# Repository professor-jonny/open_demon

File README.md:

# Open Demon Project

## Overview:
This project is an open-source recreation of the Team Xecuter Demon, a powerful multi-function NAND device for the Xbox 360. Our goal is to rebuild the firmware, fix existing bugs, and potentially develop new hardware add-ons. We hope this project encourages wider community involvement.

## Demon background:
Released in February 2012 alongside a J-Runner update, the Demon offered an all-in-one solution for NAND programming. While initially successful, it was perhaps over-hyped and ultimately didn't achieve the same market penetration as other Team Xecuter devices. The rise of stealth services further diminished its relevance, and the lack of promised add-on hardware hampered its potential. Numerous planned add-ons never saw a public release due to Team Xecuter's internal challenges. Following financial and legal difficulties, ownership transitioned from K3 to Max.

The Demon provides access to the console's UART for direct interaction, along with extensive onboard I/O capable of supporting a separate 8-bit bus. Additional I/O pins are available for bit-banging SPI, I2C, or other protocols. Although Team Xecuter announced Android and iOS remote control apps in July 2012, these were never released. Similarly, LCD support was explored, with prototypes circulated among developers, but only the NAND switching plugin, Switch!, was officially launched.

## Project Background:
Inspired by discussions with fellow enthusiasts and analysis of the Xbox 360 ODE cracking process, this project began with recreating the Demon's schematics. Access to images of a pre-release slim PCB aided in verification.

Understanding the hardware, components, and design is crucial for reverse engineering. One undocumented aspect is controlling the Demon's hardware and I/O from the console. We aim to document the I/O addressing scheme (if implemented) and investigate the potential for a UART control API. A PC-based USB control API already exists. Third-party add-ons could leverage the Demon's I/O, potentially enabling features like an integrated LCD display.

## Theory of operation:
The Demon's NAND interface largely mirrors the console's onboard NAND, using a tri-state bus transceiver to isolate the microcontroller from the NAND control logic. Control appears to rely on the CE and RB signals, with other control lines interrupted by the transceiver. Logic in U3 prevents simultaneous driving of both CE pins. C3 likely introduces timing delays for CE switching to the Demon's NAND via NOR gates in U4. This, combined with RB, likely determines chip readiness before OE activates, hijacking CE to enable the Demon's NAND. OE also enables the tri-state transceiver and Demon's NAND CE logic when the motherboard's CE is high.

The design seemingly intercepts NAND control between read/write cycles, asserting and locking control while the chip is busy. Analyzing microcontroller-to-NAND communication is necessary for confirmation, but this theory appears plausible.

## Challenges:
The AT90USB microcontroller's bootloader employs custom encryption (believed to be RSA-2048), posing significant challenges. Existing Team Xecuter firmware is unanalyzable, current devices require a bootloader update for compatibility, and a new bootloader would break existing firmware support. Developing new firmware for the current bootloader is blocked by signature checks.

Project advancement hinges on recovering the bootloader or its RSA key. Collaboration with experienced individuals is sought. Donations are welcome to support this effort. While various options have been considered, we remain open to suggestions. Contact is being attempted with the original Team Xecuter developer. Interest exists in manufacturing the device if the bootloader is recovered. Due to on-the-fly firmware unpacking, direct firmware analysis is infeasible. A brown-out reset glitch or physical access is likely required for bootloader recovery. Cracking the RSA key is computationally infeasible.

For this project to go forward I would like to recover the bootloader or at least the RSA key by attacking the microcontroller if any one has experience with this or would be willing to try this it would be awesome if you would contact me.
I don't fancy dropping $1400usd to a chineese firm to do this I would rather give this to a fellow Xbox or scene hacker as this is beyond my skill and a very special area.
I already have a few buddies who would be willing to donate to the cause, So far I have resisted going down the route of croud sourcing the project as realistically I don't think niche projects like this work well on that platform and i'd like to aviod the disapointment for everyone when it fails.
You are welcome to donate to the cause if you wish id love a failed demon hardware so i can fully recreate PCB's.

I'd like to keep it all open source if possible, or it close it for a time to make hardware to recoup costs if we were to fund bootloader recovery there is a whole lot of options I have not explored here and I'm open to suggestions.

I have atempted to contact the original Team Xecuter dev involved with the design and programming of the demon project but have had no luck in getting a reply sadly so it is what it is.

I already have people intrested in manufacturing the device if we do manage to progress futher and recover the bootloader there is intrest to recreate them.

The demon seems to unpack the firmware on the fly and write it to the onbord flash so there is no attack vector there and we would need to preform brown out reset glitch or physical access to recover the bootloader for reverse engineering to get the RSA key.

RSA is currently secure and would take a supercomputer decades to crack the firmware update key embeded within the bootloader.

## Project Outline/ Future Plans:
The future plan is to recrate the 
The primary goal is an open-source Demon recreation, initially compatible with existing hardware. A hardware revision is likely due to component discontinuation. A more ambitious objective involves a new FPGA-based device with a microcontroller. This would enable on-the-fly NAND image creation, kernel patching, and a console configuration app. A shared memory window could facilitate console-microcontroller communication for RAM offloading, code relocation, and coprocessing.

Eaton's testing indicates a NAND bus speed of approximately 1.4 Mbps, suitable for low-bandwidth operations. The impact of using faster media is unknown. This advanced design requires skilled FPGA/CPLD developers. More information is available on 

Eaton's blog:
[eaton works](https://eaton-works.com/2023/01/09/how-microsoft-attempted-to-make-the-xbox-360-dashboard-load-faster/)

The schematics were designed using Eagle:
[Autodesk Eagle]( https://www.autodesk.com/products/eagle/free-download)

## Licensing
This project is open-source. Hardware and schematics are licensed under the [CERN OHL v.2.0.](https://ohwr.org/cernohl).

Donations are welcome to support XBMC4XBOX, Team Resurgent, or other Xbox resources.

[Teamresurgent donate]( https://www.patreon.com/teamresurgent)
[xbmc4xbox donate](https://www.xbmc4xbox.org.uk/donate/)

## Disclaimer
This project is a work in progress and may contain inaccuracies. Feedback and corrections are welcome. Development is ongoing, and Gerber files for all Demon variants will be released eventually. A preliminary Phat PCB design is available.
This project is by no meany complete or possibly accurate it is my own account of insight may be incorect, and I'm open to suggestions and correctons.

## Acknowledgements
We thank Coz, Goobycorp, and Eaton for their invaluable contributions.

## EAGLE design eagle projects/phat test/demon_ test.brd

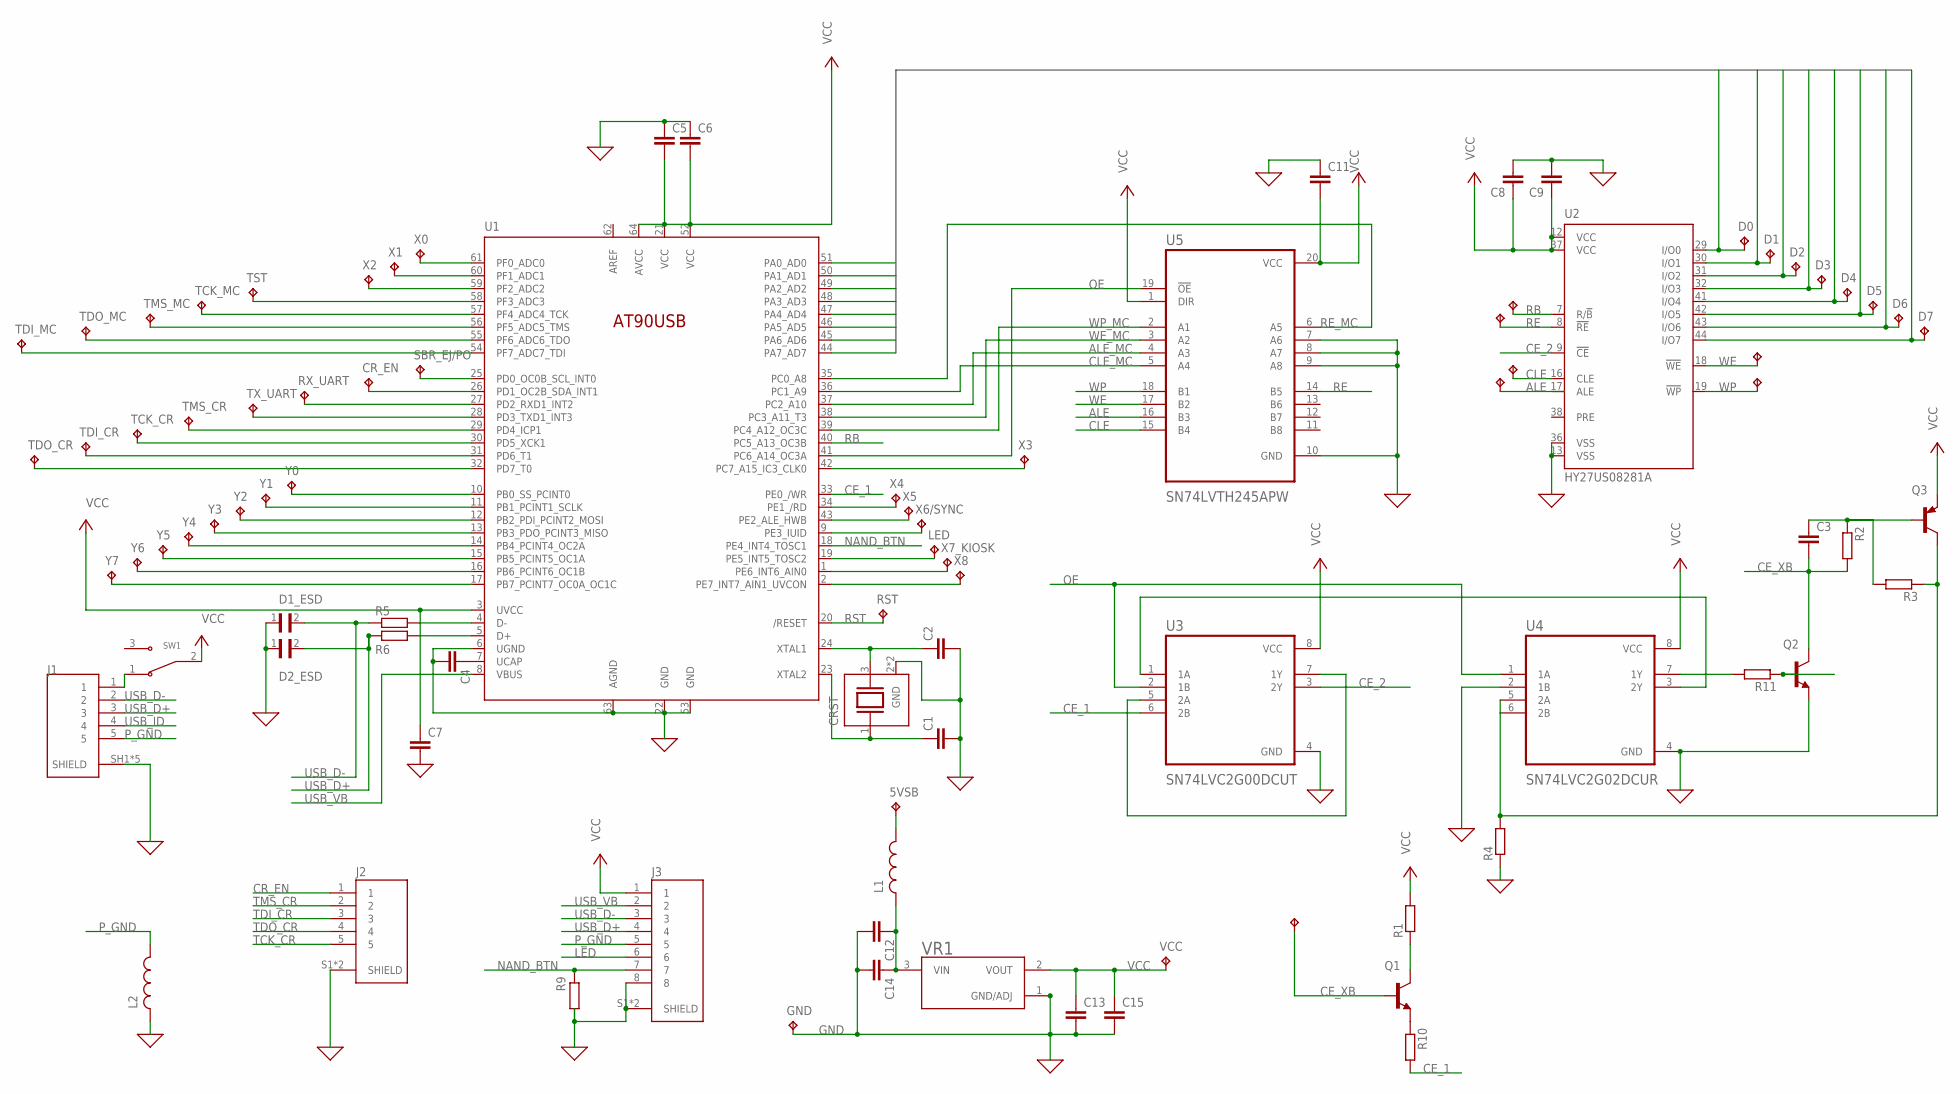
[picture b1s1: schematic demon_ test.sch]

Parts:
5VSB: TPTP20R; TP20R
ALE1: TPTP15R; TP15R
C1, C2: 18pf; C0603
C3: 47pf; C0603
C4, C11: 1uf; C0603
C5, C6, C7, C8, C9, C12: .1uf; C0603
C13: 2.2uf tant; C2012
C14: 1uf tant; C2012
C15: 10uf Tant; C2012
CE: TPTP15R; TP15R
CLE1: TPTP15R; TP15R
CRST: ABMM2-8.000MHZ-E2-T; XTAL_ABMM2-8.000MHZ-E2-T
CR_EN: TPTP15R; TP15R
D0, D1, D2, D3, D4, D5, D6, D7: TPTP15R; TP15R
D1_ESD, D2_ESD: PGB1010603; ESD_PGB1010603MR
GND: TPTP15R; TP15R
J1: UJ2-MIBH2-4-SMT; CUI_UJ2-MIBH2-4-SMT
J2: FFC3B07-05-T; GCT_FFC3B07-05-T
J3: FFC3B07-08-T; GCT_FFC3B07-08-T
L1, L2: LQW2BAS6N8J00L; INDC2015X152N
LED: TPTP15R; TP15R
Q1, Q2: BC846; SOT23
Q3: bc856; SOT23-BEC
R1, R6: 22R 5%; R0603
R2: 470R 5%; R0603
R3: 2k7R 5%; R0603
R4: 330R 5%; R0603
R5: 22r 5%; R0603
R9: 10kR 5%; R0603
R10: 68R 5%; R0603
R11: 680R 5%; R0603
RB1: TPTP15R; TP15R
RE: TPTP15R; TP15R
RST: TPTP15R; TP15R
RX_UART: TPTP15R; TP15R
SBR_EJ/PO: TPTP15R; TP15R
SW1: EG1215AA; SW_EG1215AA
TCK_CR: TPTP15R; TP15R
TCK_MC: TPTP15R; TP15R
TDI_CR: TPTP15R; TP15R
TDI_MC: TPTP15R; TP15R
TDO_CR: TPTP15R; TP15R
TDO_MC: TPTP15R; TP15R
TMS_CR: TPTP15R; TP15R
TMS_MC: TPTP15R; TP15R
TST: TPTP15R; TP15R
TX_UART: TPTP15R; TP15R
U1: AT90USB-QFN; QFN64
U2: HY27US08281A; TSOP48
U3: SN74LVC2G00DCUT; SOP50P310X90-8N
U4: SN74LVC2G02DCUR; SOP50P310X90-8N
U5: SN74LVTH245APW; SOP65P640X120-20N
VCC: TPTP15R; TP15R
VR1: AMS1117-3.3; SOT229P700X180-4N
WE1: TPTP15R; TP15R
WP1: TPTP15R; TP15R
X0, X1, X2, X3, X4, X5, X6/SYNC, X7_KIOSK, X8: TPTP15R; TP15R
Y0, Y1, Y2, Y3, Y4, Y5, Y6, Y7: TPTP15R; TP15R

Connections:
0: C7.2, U5.7 (A6), U5.8 (A7), U5.9 (A8), U5.10 (GND)
ALE: ALE1.TP, U2.17 (ALE), U5.16 (B3)
ALE_MC: U1.37 (PC2_A10), U5.4 (A3)
AREF: U1.62 (AREF)
CE_1: R10.2, U1.33 (PE0_/WR), U3.6 (2B)
CE_2: U2.9 (!CE), U3.3 (2Y)
CE_XB: C3.2, CE.TP, Q1.1 (B), Q2.3 (C), R2.2
CLE: CLE1.TP, U2.16 (CLE), U5.15 (B4)
CLE_MC: U1.36 (PC1_A9), U5.5 (A4)
CR_EN: CR_EN.TP, J2.1, U1.26 (PD1_OC2B_SDA_INT1)
D0: D0.TP, U1.51 (PA0_AD0), U2.29 (I/O0)
D1: D1.TP, U1.50 (PA1_AD1), U2.30 (I/O1)
D2: D2.TP, U1.49 (PA2_AD2), U2.31 (I/O2)
D3: D3.TP, U1.48 (PA3_AD3), U2.32 (I/O3)
D4: D4.TP, U1.47 (PA4_AD4), U2.41 (I/O4)
D5: D5.TP, U1.46 (PA5_AD5), U2.42 (I/O5)
D6: D6.TP, U1.45 (PA6_AD6), U2.43 (I/O6)
D7: D7.TP, U1.44 (PA7_AD7), U2.44 (I/O7)
F_5VSB: C12.1, C14.1, L1.1, VR1.3 (VIN)
GND: C1.2, C2.2, C4.2, C5.1, C6.1, C8.2, C9.2, C11.1, C12.2, C13.2, C14.2, C15.2, CRST.2 (GND), CRST.4 (GND), D1_ESD.1, D2_ESD.1, GND.TP, J1.SH1 (SHIELD), J1.SH2 (SHIELD), J1.SH3 (SHIELD), J1.SH4 (SHIELD), J1.SH5 (SHIELD), J2.S1 (SHIELD), J2.S2 (SHIELD), J3.8, J3.S1 (SHIELD), J3.S2 (SHIELD), L2.1, Q2.2 (E), R4.1, R9.2, U1.6 (UGND), U1.22 (GND), U1.53 (GND), U1.63 (AGND), U2.13 (VSS), U2.36 (VSS), U3.4 (GND), U4.2 (1B), U4.4 (GND), VR1.1 (GND/ADJ)
LED: J3.6, LED.TP, U1.19 (PE5_INT5_TOSC2)
unnamed: R5.2, U1.4 (D-)
unnamed: C3.1, Q3.B, R2.1, R3.2
unnamed: C4.1, U1.7 (UCAP)
unnamed: R6.2, U1.5 (D+)
unnamed: Q1.3 (C), R1.1
unnamed: Q1.2 (E), R10.1
unnamed: 5VSB.TP, L1.2
unnamed: U3.5 (2A), U3.7 (1Y)
unnamed: U3.1 (1A), U4.3 (2Y)
unnamed: R11.2, U4.7 (1Y)
unnamed: Q2.1 (B), R11.1
unnamed: Q3.C, R3.1, R4.2, U4.5 (2A), U4.6 (2B)
unnamed: J1.1, SW1.1
NAND_BTN: J3.7, R9.1, U1.18 (PE4_INT4_TOSC1)
OE: U1.41 (PC6_A14_OC3A), U3.2 (1B), U4.1 (1A), U5.19 (!OE)
P_GND: J1.5, J3.5, L2.2
RB: RB1.TP, U1.40 (PC5_A13_OC3B), U2.7 (R/!B)
RE: RE.TP, U2.8 (!RE), U5.14 (B5)
RE_MC: U1.35 (PC0_A8), U5.6 (A5)
RST: RST.TP, U1.20 (/RESET)
RX_UART: RX_UART.TP, U1.27 (PD2_RXD1_INT2)
SBR: SBR_EJ/PO.TP, U1.25 (PD0_OC0B_SCL_INT0)
TCK_CR: J2.5, TCK_CR.TP, U1.30 (PD5_XCK1)
TCK_MC: TCK_MC.TP, U1.57 (PF4_ADC4_TCK)
TD0_MC: TDO_MC.TP, U1.55 (PF6_ADC6_TDO)
TDI_CR: J2.3, TDI_CR.TP, U1.31 (PD6_T1)
TDI_MC: TDI_MC.TP, U1.54 (PF7_ADC7_TDI)
TDO_CR: J2.4, TDO_CR.TP, U1.32 (PD7_T0)
TMS_CR: J2.2, TMS_CR.TP, U1.29 (PD4_ICP1)
TMS_MC: TMS_MC.TP, U1.56 (PF5_ADC5_TMS)
TST: TST.TP, U1.58 (PF3_ADC3)
TX_UART: TX_UART.TP, U1.28 (PD3_TXD1_INT3)
USB_D+: D2_ESD.2, J1.3, J3.4, R6.1
USB_D-: D1_ESD.2, J1.2, J3.3, R5.1
USB_ID: J1.4
USB_VB: J3.2, U1.8 (VBUS)
VCC: C5.2, C6.2, C7.1, C8.1, C9.1, C11.2, C13.1, C15.1, J3.1, Q3.E, R1.2, SW1.2, U1.3 (UVCC), U1.21 (VCC), U1.52 (VCC), U1.64 (AVCC), U2.12 (VCC), U2.37 (VCC), U3.8 (VCC), U4.8 (VCC), U5.1 (DIR), U5.20 (VCC), VCC.TP, VR1.2 (VOUT)
WE: U2.18 (!WE), U5.17 (B2), WE1.TP
WE_MC: U1.38 (PC3_A11_T3), U5.3 (A2)
WP: U2.19 (!WP), U5.18 (B1), WP1.TP
WP_MC: U1.39 (PC4_A12_OC3C), U5.2 (A1)
X0: U1.61 (PF0_ADC0), X0.TP
X1: U1.60 (PF1_ADC1), X1.TP
X2: U1.59 (PF2_ADC2), X2.TP
X3: U1.42 (PC7_A15_IC3_CLK0), X3.TP
X4: U1.34 (PE1_/RD), X4.TP
X5: U1.43 (PE2_ALE_HWB), X5.TP
X6/SYNC: U1.9 (PE3_IUID), X6/SYNC.TP
X7: U1.1 (PE6_INT6_AIN0), X7_KIOSK.TP
X8: U1.2 (PE7_INT7_AIN1_UVCON), X8.TP
XTAL1: C2.1, CRST.3 (2), U1.24 (XTAL1)
XTAL2: C1.1, CRST.1, U1.23 (XTAL2)
Y0: U1.10 (PB0_SS_PCINT0), Y0.TP
Y1: U1.11 (PB1_PCINT1_SCLK), Y1.TP
Y2: U1.12 (PB2_PDI_PCINT2_MOSI), Y2.TP
Y3: U1.13 (PB3_PDO_PCINT3_MISO), Y3.TP
Y4: U1.14 (PB4_PCINT4_OC2A), Y4.TP
Y5: U1.15 (PB5_PCINT5_OC1A), Y5.TP
Y6: U1.16 (PB6_PCINT6_OC1B), Y6.TP
Y7: U1.17 (PB7_PCINT7_OC0A_OC1C), Y7.TP

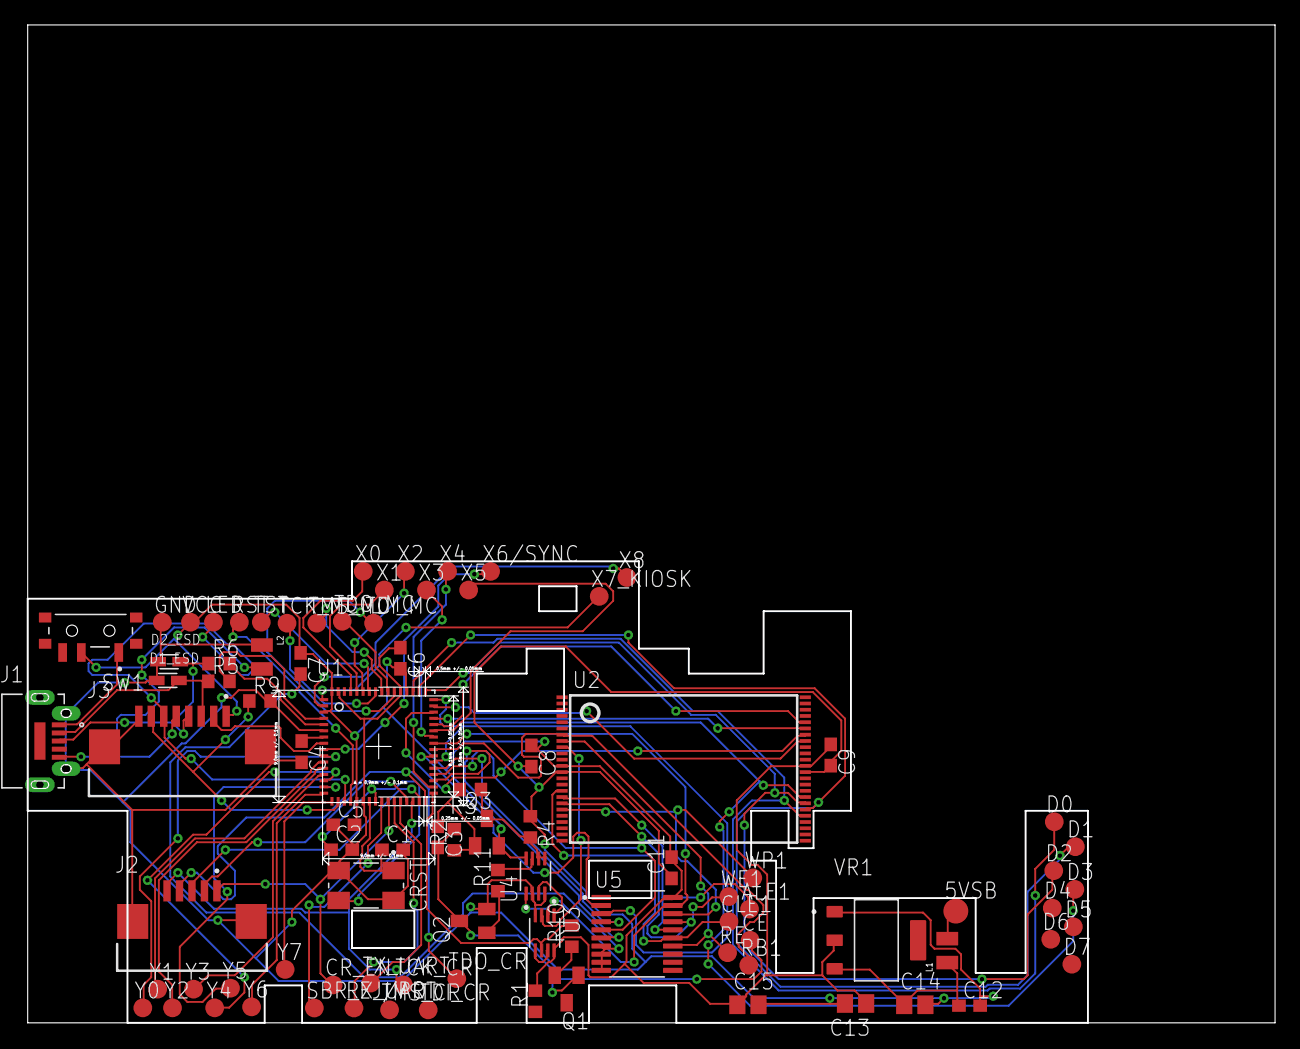
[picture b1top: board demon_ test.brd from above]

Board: 2 copper layers, 99.9 x 79.9 mm, 91 parts (0 on the bottom side), 79 nets.

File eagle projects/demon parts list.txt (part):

Partlist

Exported from demon.sch at 27/03/2023 12:23 pm

EAGLE Version 9.6.2 Copyright (c) 1988-2020 Autodesk, Inc.

Assembly variant: 

Part      Value               Device               Package                  Library                   Sheet

5VSB      TPTP20R             TPTP20R              TP20R                    testpad                   1
ALE1      TPTP15R             TPTP15R              TP15R                    testpad                   1
C1        18pf                C-EUC0603            C0603                    rcl                       1
C2        18pf                C-EUC0603            C0603                    rcl                       1
C3        47pf                C-EUC0603            C0603                    rcl                       1
C4        1uf                 C-EUC0603            C0603                    rcl                       1
C5        .1uf                C-EUC0603            C0603                    rcl                       1
C6        .1uf                C-EUC0603            C0603                    rcl                       1
C7        .1uf                C-EUC0603            C0603                    rcl                       1
C8        .1uf                C-EUC0603            C0603                    rcl                       1
C9        .1uf                C-EUC0603            C0603                    rcl                       1
C11       1uf                 C-EUC0603            C0603                    rcl                       1
C12       .1uf                C-EUC0603            C0603                    rcl                       1
C13       2.2uf tant          CC2012               C2012                    eagle-ltspice             1
C14       1uf tant            CC2012               C2012                    eagle-ltspice             1
C15       10uf Tant           CC2012               C2012                    eagle-ltspice             1
CE        TPTP15R             TPTP15R              TP15R                    testpad                   1
CLE1      TPTP15R             TPTP15R              TP15R                    testpad                   1
CRST      ABMM2-8.000MHZ-E2-T ABMM2-8.000MHZ-E2-T  XTAL_ABMM2-8.000MHZ-E2-T ABMM2-8.000MHZ-E2-T       1
CR_EN     TPTP15R             TPTP15R              TP15R                    testpad                   1
D0        TPTP15R             TPTP15R              TP15R                    testpad                   1
D1        TPTP15R             TPTP15R              TP15R                    testpad                   1
D1_ESD    PGB1010603          PGB1010603           ESD_PGB1010603MR         PGB1010603                1
D2        TPTP15R             TPTP15R              TP15R                    testpad                   1
D2_ESD    PGB1010603          PGB1010603           ESD_PGB1010603MR         PGB1010603                1
D3        TPTP15R             TPTP15R              TP15R                    testpad                   1
D4        TPTP15R             TPTP15R              TP15R                    testpad                   1
D5        TPTP15R             TPTP15R              TP15R                    testpad                   1
D6        TPTP15R             TPTP15R              TP15R                    testpad                   1
D7        TPTP15R             TPTP15R              TP15R                    testpad                   1
GND       TPTP15R             TPTP15R              TP15R                    testpad                   1
J1        UJ2-MIBH2-4-SMT     UJ2-MIBH2-4-SMT      CUI_UJ2-MIBH2-4-SMT      UJ2-MIBH2-4-SMT           1
J2        FFC3B07-05-T        FFC3B07-05-T         GCT_FFC3B07-05-T         FFC3B07-05-T              1
J3        FFC3B07-08-T        FFC3B07-08-T         GCT_FFC3B07-08-T         FFC3B07-08-T              1
L1        LQW2BAS6N8J00L      LQW2BAS6N8J00L       INDC2015X152N            LQW2BAS6N8J00L            1
L2        LQW2BAS6N8J00L      LQW2BAS6N8J00L       INDC2015X152N            LQW2BAS6N8J00L            1
LED       TPTP15R             TPTP15R              TP15R                    testpad                   1
Q1        BC846               BC846                SOT23                    transistor                1
Q2        BC846               BC846                SOT23                    transistor                1
Q3        bc856               BC856A-PNP-SOT23-BEC SOT23-BEC                transistor                1
R1        22R 5%              R-EU_R0603           R0603                    resistor                  1
R2        470R 5%             R-EU_R0603           R0603                    resistor                  1
R3        2k7R 5%             R-EU_R0603           R0603                    resistor                  1
R4        330R 5%             R-EU_R0603           R0603                    resistor                  1
R5        22r 5%              R-EU_R0603           R0603                    resistor                  1
R6        22R 5%              R-EU_R0603           R0603                    resistor                  1
R9        10kR 5%             R-EU_R0603           R0603                    resistor                  1
R10       68R 5%              R-EU_R0603           R0603                    resistor                  1
R11       680R 5%             R-EU_R0603           R0603                    resistor                  1
RB1       TPTP15R             TPTP15R              TP15R                    testpad                   1
RE        TPTP15R             TPTP15R              TP15R                    testpad                   1
RST       TPTP15R             TPTP15R              TP15R                    testpad                   1
RX_UART   TPTP15R             TPTP15R              TP15R                    testpad                   1
SBR_EJ/PO TPTP15R             TPTP15R              TP15R                    testpad                   1
SW1       EG1215AA            EG1215AA             SW_EG1215AA              EG1215AA                  1
TCK_CR    TPTP15R             TPTP15R              TP15R                    testpad                   1
TCK_MC    TPTP15R             TPTP15R              TP15R                    testpad                   1
TDI_CR    TPTP15R             TPTP15R              TP15R                    testpad                   1
TDI_MC    TPTP15R             TPTP15R              TP15R                    testpad                   1
TDO_CR    TPTP15R             TPTP15R              TP15R                    testpad                   1
TDO_MC    TPTP15R             TPTP15R              TP15R                    testpad                   1
TMS_CR    TPTP15R             TPTP15R              TP15R                    testpad                   1
TMS_MC    TPTP15R             TPTP15R              TP15R                    testpad                   1
TST       TPTP15R             TPTP15R              TP15R                    testpad                   1
TX_UART   TPTP15R             TPTP15R              TP15R                    testpad                   1
U1                            AT90USB-QFN          QFN64                    controller-micro_atmel_jd 1
U2        HY27US08281A        HY27US08281A         TSOP48                   memory-hynix              1
U3        SN74LVC2G00DCUT     SN74LVC2G00DCUT      SOP50P310X90-8N          SN74LVC2G00DCUT           1
U4        SN74LVC2G02DCUR     SN74LVC2G02DCUR      SOP50P310X90-8N          SN74LVC2G02DCUR           1
U5        SN74LVTH245APW      SN74LVTH245APW       SOP65P640X120-20N        SN74LVTH245APW            1
VCC       TPTP15R             TPTP15R              TP15R                    testpad                   1
VR1       AMS1117-3.3         AMS1117-3.3          SOT229P700X180-4N        AMS1117-3.3               1
WE1       TPTP15R             TPTP15R              TP15R                    testpad                   1
WP1       TPTP15R             TPTP15R              TP15R                    testpad                   1
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
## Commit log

2023-04-06 initial import
    Initial project import
2023-04-06 Update README.md
    Update README.md
2023-04-06 edit
2023-04-11 Add pictures
    Add Slim proto pictures
    Thanks [CoZ]
2024-11-15 Update README.md
    Docs: Rewrote README for improved clarity, grammar, and style. Addressed issues with sentence structure, word choice, and technical explanations.
    README: Comprehensive rewrite focusing on clarity and conciseness. Improved technical descriptions and addressed potential ambiguities. Formalized language and improved overall flow.
    Documentation: Overhauled README to enhance readability for a wider audience. Clarified technical details, corrected grammar and spelling, and adopted a more professional tone.
2024-11-15 Update README.md
    Moved schematic images back to the beginning of the README. They were previously moved, but this placement provides better initial context for the project.
